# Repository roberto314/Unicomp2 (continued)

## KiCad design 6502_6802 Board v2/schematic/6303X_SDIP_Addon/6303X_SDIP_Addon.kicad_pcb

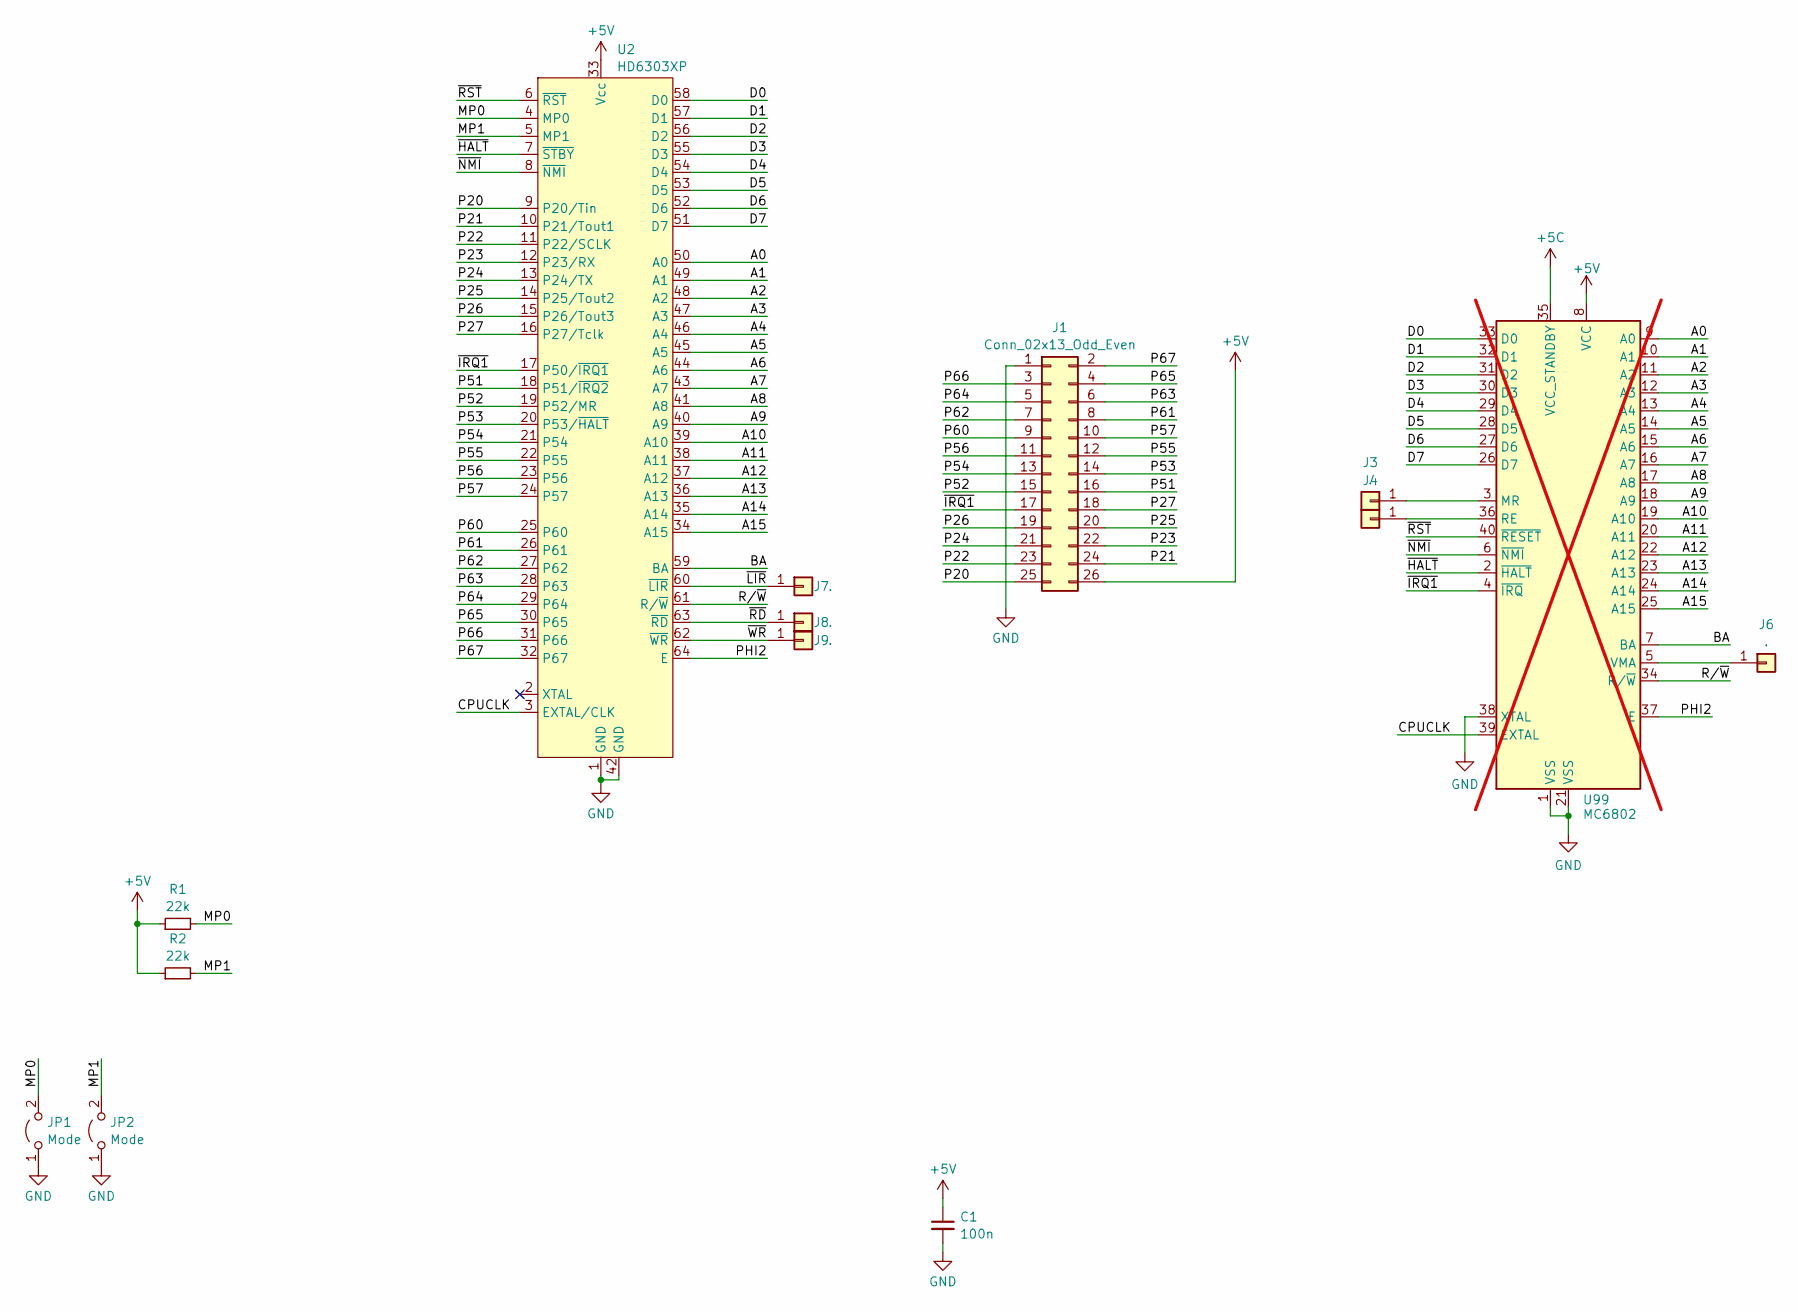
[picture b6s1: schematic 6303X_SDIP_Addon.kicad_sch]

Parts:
C1: 100n; C_1206_3216Metric_Pad1.33x1.80mm_HandSolder
J1: Conn_02x13_Odd_Even; PinHeader_2x13_P2.54mm_Horizontal
J3, J4, J6, J7, J8, J9: .; PinHeader_1x01_P2.00mm_Vertical
JP1, JP2: Mode; PinHeader_1x02_P2.54mm_Vertical
R1, R2: 22k; R_1206_3216Metric_Pad1.30x1.75mm_HandSolder
U2: HD6303XP; DIP-64_W19.05mm_P1.77
U99: MC6802; DIP-40_W15.24mm; not fitted

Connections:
+5V: C1.1, J1.26, R1.1, R2.1, U2.33 (Vcc); also elsewhere on the board
/A0: U2.50 (A0); also elsewhere on the board
/A1: U2.49 (A1); also elsewhere on the board
/A2: U2.48 (A2); also elsewhere on the board
/A3: U2.47 (A3); also elsewhere on the board
/A4: U2.46 (A4); also elsewhere on the board
/A5: U2.45 (A5); also elsewhere on the board
/A6: U2.44 (A6); also elsewhere on the board
/A7: U2.43 (A7); also elsewhere on the board
/A8: U2.41 (A8); also elsewhere on the board
/A9: U2.40 (A9); also elsewhere on the board
/A10: U2.39 (A10); also elsewhere on the board
/A11: U2.38 (A11); also elsewhere on the board
/A12: U2.37 (A12); also elsewhere on the board
/A13: U2.36 (A13); also elsewhere on the board
/A14: U2.35 (A14); also elsewhere on the board
/A15: U2.34 (A15); also elsewhere on the board
/BA: U2.59 (BA); also elsewhere on the board
/CPUCLK: U2.3 (EXTAL/CLK); also elsewhere on the board
/D0: U2.58 (D0); also elsewhere on the board
/D1: U2.57 (D1); also elsewhere on the board
/D2: U2.56 (D2); also elsewhere on the board
/D3: U2.55 (D3); also elsewhere on the board
/D4: U2.54 (D4); also elsewhere on the board
/D5: U2.53 (D5); also elsewhere on the board
/D6: U2.52 (D6); also elsewhere on the board
/D7: U2.51 (D7); also elsewhere on the board
/MP0: JP1.2 (B), R1.2, U2.4 (MP0)
/MP1: JP2.2 (B), R2.2, U2.5 (MP1)
/P20: J1.25, U2.9 (P20/Tin)
/P21: J1.24, U2.10 (P21/Tout1)
/P22: J1.23, U2.11 (P22/SCLK)
/P23: J1.22, U2.12 (P23/RX)
/P24: J1.21, U2.13 (P24/TX)
/P25: J1.20, U2.14 (P25/Tout2)
/P26: J1.19, U2.15 (P26/Tout3)
/P27: J1.18, U2.16 (P27/Tclk)
/P51: J1.16, U2.18 (P51/~IRQ2)
/P52: J1.15, U2.19 (P52/MR)
/P53: J1.14, U2.20 (P53/~HALT)
/P54: J1.13, U2.21 (P54)
/P55: J1.12, U2.22 (P55)
/P56: J1.11, U2.23 (P56)
/P57: J1.10, U2.24 (P57)
/P60: J1.9, U2.25 (P60)
/P61: J1.8, U2.26 (P61)
/P62: J1.7, U2.27 (P62)
/P63: J1.6, U2.28 (P63)
/P64: J1.5, U2.29 (P64)
/P65: J1.4, U2.30 (P65)
/P66: J1.3, U2.31 (P66)
/P67: J1.2, U2.32 (P67)
/PHI2: U2.64 (E); also elsewhere on the board
/R/~W: U2.61 (R/~W); also elsewhere on the board
/~HALT: U2.7 (~STBY); also elsewhere on the board
/~IRQ1: J1.17, U2.17 (P50/~IRQ1); also elsewhere on the board
/~LIR: J7.1, U2.60 (~LIR)
/~NMI: U2.8 (~NMI); also elsewhere on the board
/~RD: J8.1, U2.63 (~RD)
/~RST: U2.6 (~RST); also elsewhere on the board
/~WR: J9.1, U2.62 (~WR)
GND: C1.2, J1.1, JP1.1 (A), JP2.1 (A), U2.1 (GND), U2.42 (GND); also elsewhere on the board
unnamed 63: J3.1; also elsewhere on the board
unnamed 64: J4.1; also elsewhere on the board
unnamed 65: J6.1; also elsewhere on the board

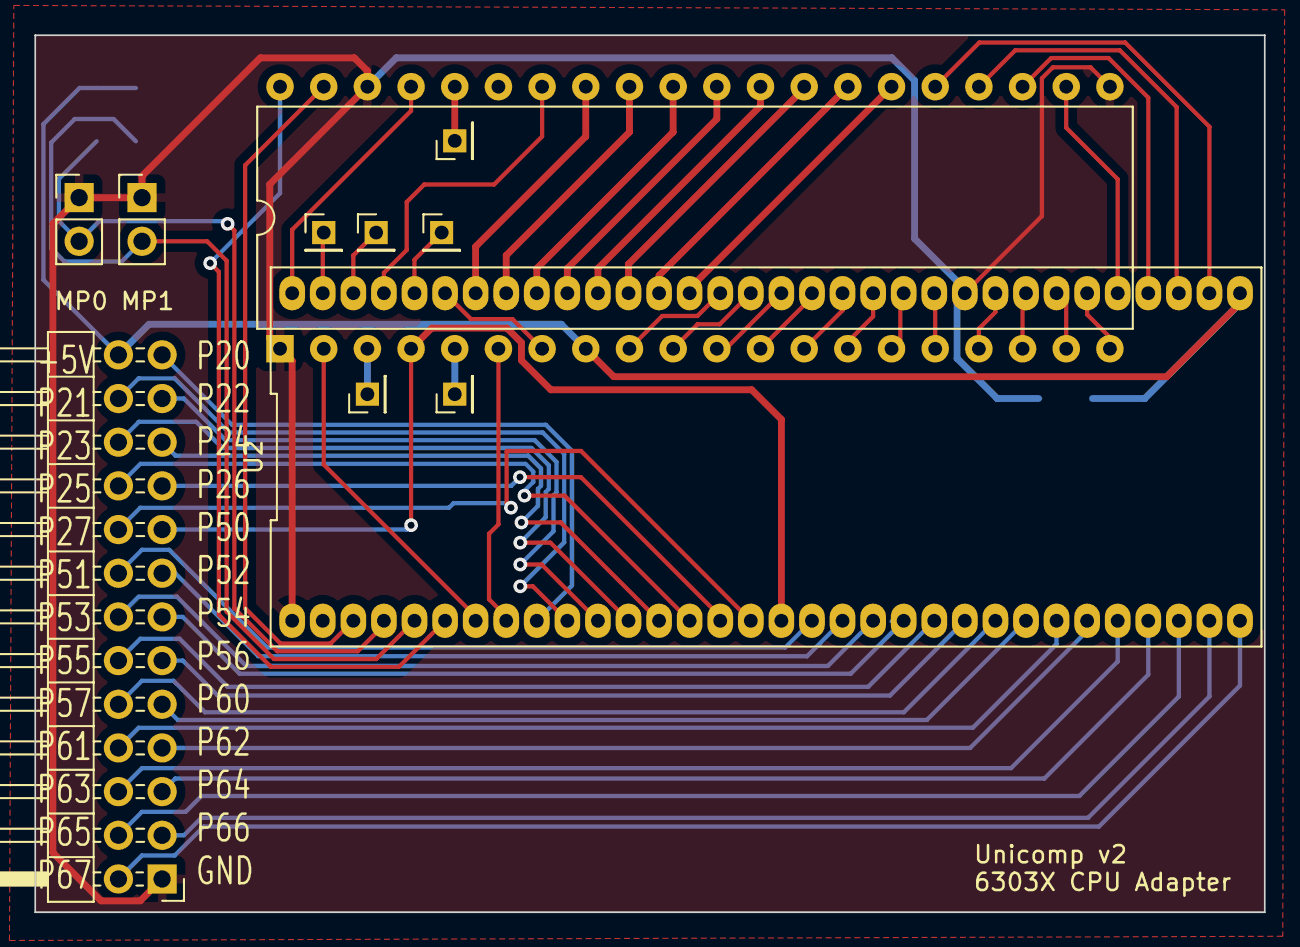
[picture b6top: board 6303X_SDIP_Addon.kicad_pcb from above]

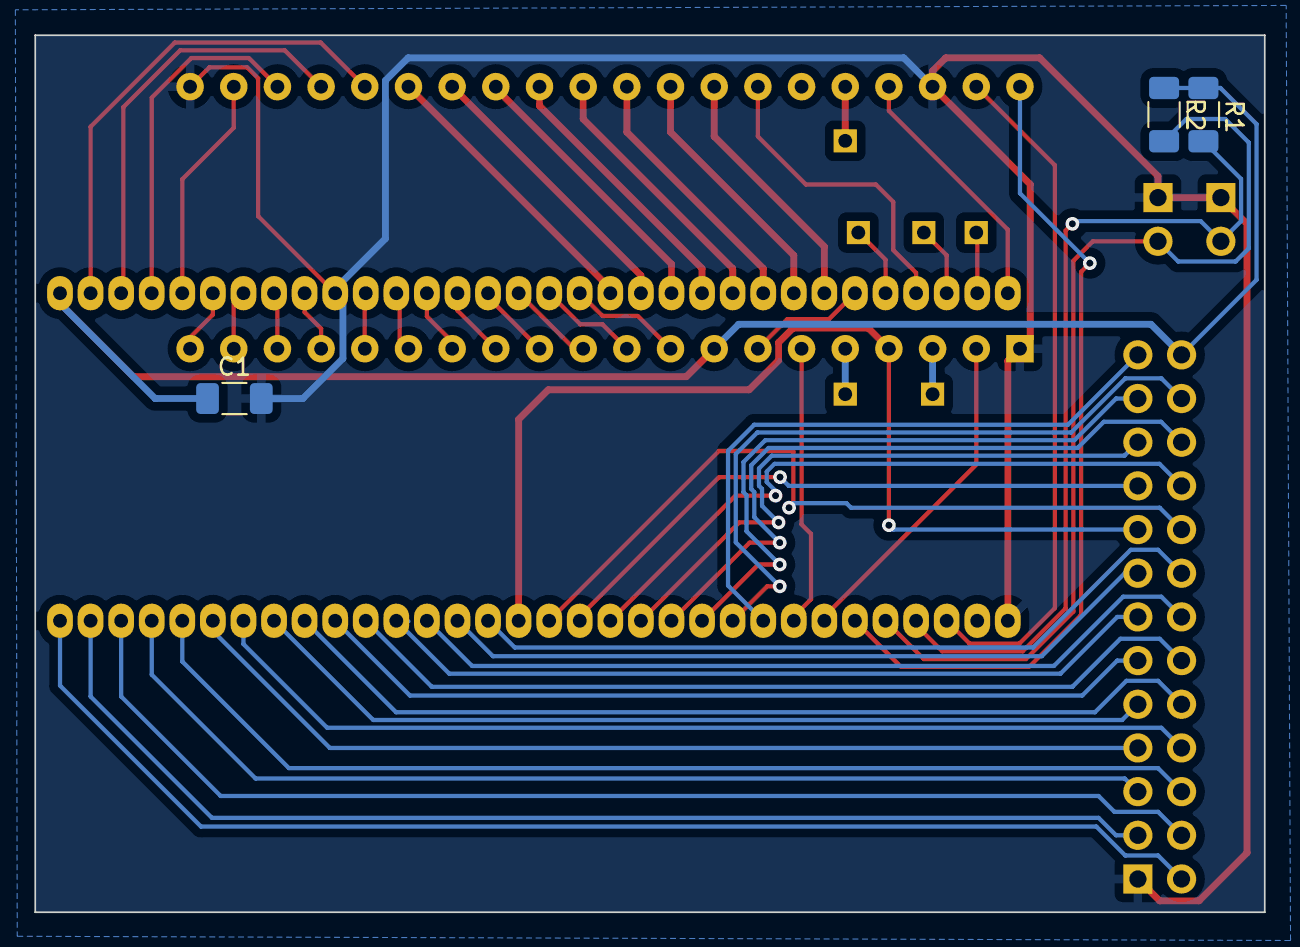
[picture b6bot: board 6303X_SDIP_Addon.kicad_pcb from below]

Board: 2 copper layers, 71.5 x 51.0 mm, 14 parts (3 on the bottom side), 65 nets.

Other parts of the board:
U3: MC6802; DIP-40_W15.24mm

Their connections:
+5V: U3.8 (VCC); also elsewhere on the board
/A0: U3.9 (A0); also elsewhere on the board
/A1: U3.10 (A1); also elsewhere on the board
/A2: U3.11 (A2); also elsewhere on the board
/A3: U3.12 (A3); also elsewhere on the board
/A4: U3.13 (A4); also elsewhere on the board
/A5: U3.14 (A5); also elsewhere on the board
/A6: U3.15 (A6); also elsewhere on the board
/A7: U3.16 (A7); also elsewhere on the board
/A8: U3.17 (A8); also elsewhere on the board
/A9: U3.18 (A9); also elsewhere on the board
/A10: U3.19 (A10); also elsewhere on the board
/A11: U3.20 (A11); also elsewhere on the board
/A12: U3.22 (A12); also elsewhere on the board
/A13: U3.23 (A13); also elsewhere on the board
/A14: U3.24 (A14); also elsewhere on the board
/A15: U3.25 (A15); also elsewhere on the board
/BA: U3.7 (BA); also elsewhere on the board
/CPUCLK: U3.39 (EXTAL); also elsewhere on the board
/D0: U3.33 (D0); also elsewhere on the board
/D1: U3.32 (D1); also elsewhere on the board
/D2: U3.31 (D2); also elsewhere on the board
/D3: U3.30 (D3); also elsewhere on the board
/D4: U3.29 (D4); also elsewhere on the board
/D5: U3.28 (D5); also elsewhere on the board
/D6: U3.27 (D6); also elsewhere on the board
/D7: U3.26 (D7); also elsewhere on the board
/PHI2: U3.37 (E); also elsewhere on the board
/R/~W: U3.34 (R/~W); also elsewhere on the board
/~HALT: U3.2 (~HALT); also elsewhere on the board
/~IRQ1: U3.4 (~IRQ); also elsewhere on the board
/~NMI: U3.6 (~NMI); also elsewhere on the board
/~RST: U3.40 (~RESET); also elsewhere on the board
GND: U3.1 (VSS), U3.21 (VSS), U3.38 (XTAL); also elsewhere on the board
unnamed 63: U3.3 (MR); also elsewhere on the board
unnamed 64: U3.36 (RE); also elsewhere on the board
unnamed 65: U3.5 (VMA); also elsewhere on the board

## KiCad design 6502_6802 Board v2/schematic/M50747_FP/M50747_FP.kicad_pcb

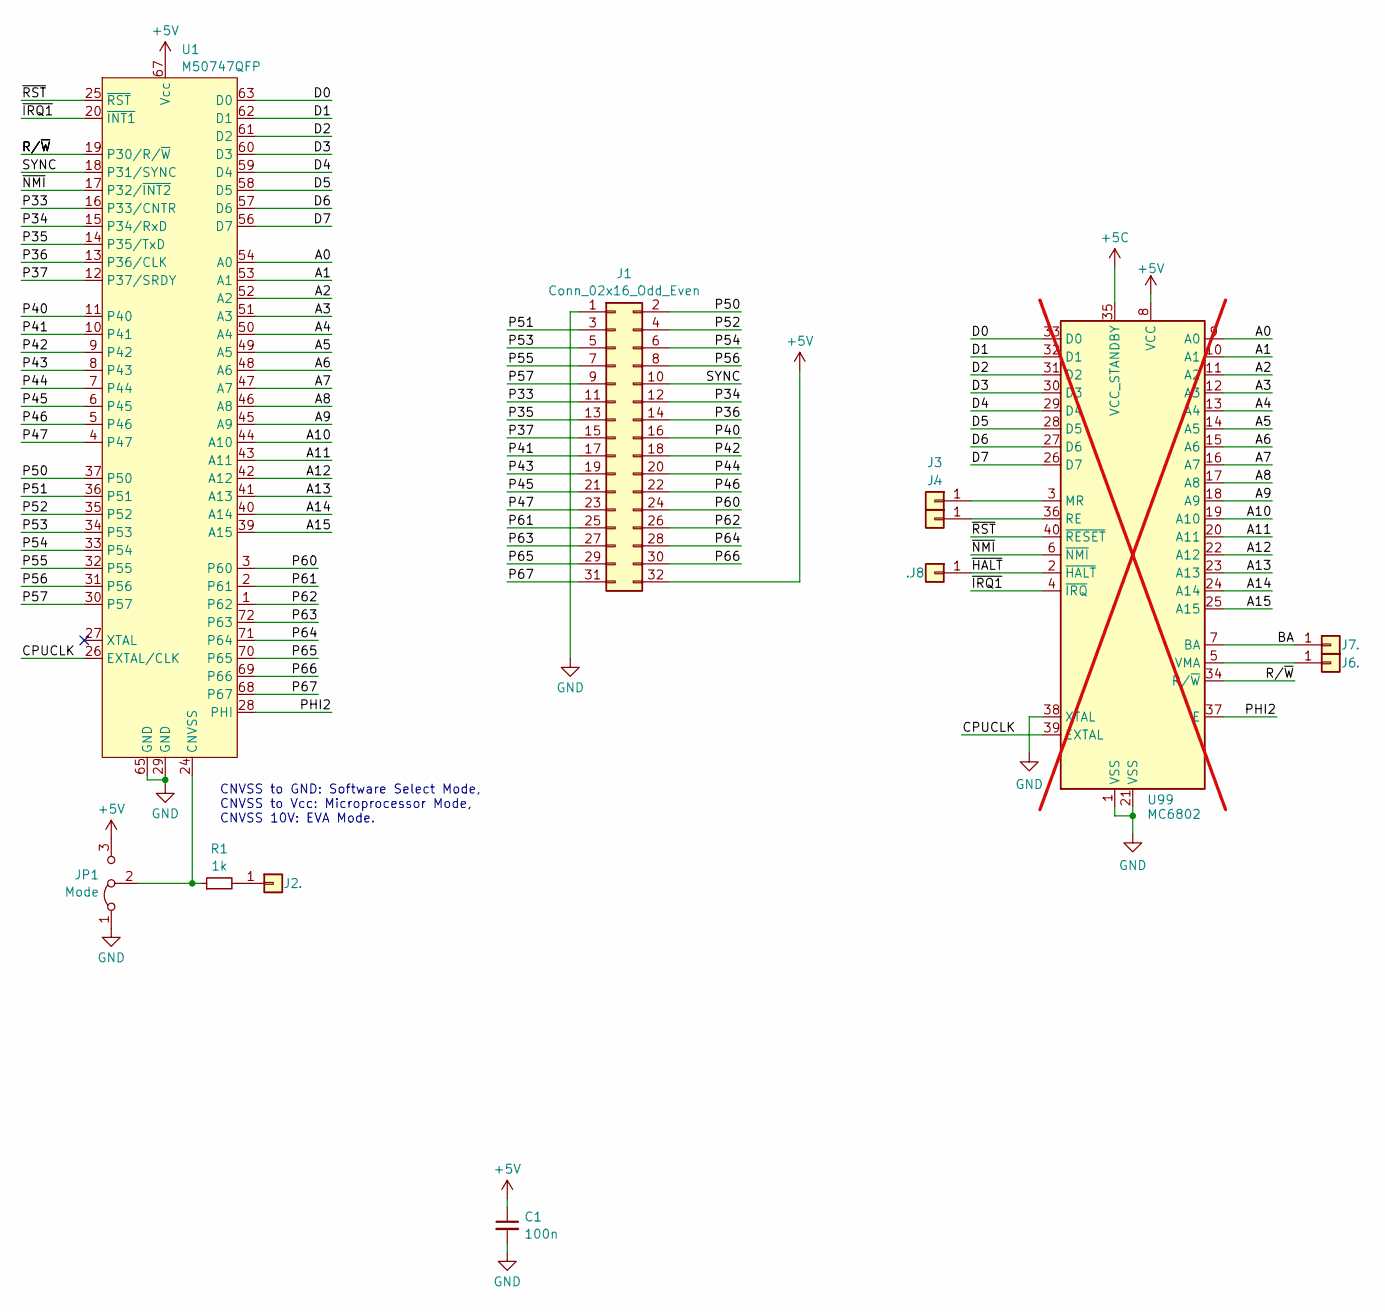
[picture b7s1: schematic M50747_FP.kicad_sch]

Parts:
C1: 100n; C_1206_3216Metric_Pad1.33x1.80mm_HandSolder
J1: Conn_02x16_Odd_Even; PinHeader_2x16_P2.54mm_Horizontal
J2, J3, J4, J6, J7, J8: .; PinHeader_1x01_P2.00mm_Vertical
JP1: Mode; SolderJumper-3_P1.3mm_Open_Pad1.0x1.5mm
R1: 1k; R_1206_3216Metric
U1: M50747QFP; QFP-72_13.2x18_Pitch0.8mm
U99: MC6802; DIP-40_W15.24mm; not fitted

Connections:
+5V: C1.1, J1.32, JP1.3 (B), U1.67 (Vcc); also elsewhere on the board
/A0: U1.54 (A0); also elsewhere on the board
/A1: U1.53 (A1); also elsewhere on the board
/A2: U1.52 (A2); also elsewhere on the board
/A3: U1.51 (A3); also elsewhere on the board
/A4: U1.50 (A4); also elsewhere on the board
/A5: U1.49 (A5); also elsewhere on the board
/A6: U1.48 (A6); also elsewhere on the board
/A7: U1.47 (A7); also elsewhere on the board
/A8: U1.46 (A8); also elsewhere on the board
/A9: U1.45 (A9); also elsewhere on the board
/A10: U1.44 (A10); also elsewhere on the board
/A11: U1.43 (A11); also elsewhere on the board
/A12: U1.42 (A12); also elsewhere on the board
/A13: U1.41 (A13); also elsewhere on the board
/A14: U1.40 (A14); also elsewhere on the board
/A15: U1.39 (A15); also elsewhere on the board
/BA: J7.1; also elsewhere on the board
/CPUCLK: U1.26 (EXTAL/CLK); also elsewhere on the board
/D0: U1.63 (D0); also elsewhere on the board
/D1: U1.62 (D1); also elsewhere on the board
/D2: U1.61 (D2); also elsewhere on the board
/D3: U1.60 (D3); also elsewhere on the board
/D4: U1.59 (D4); also elsewhere on the board
/D5: U1.58 (D5); also elsewhere on the board
/D6: U1.57 (D6); also elsewhere on the board
/D7: U1.56 (D7); also elsewhere on the board
/P33: J1.11, U1.16 (P33/CNTR)
/P34: J1.12, U1.15 (P34/RxD)
/P35: J1.13, U1.14 (P35/TxD)
/P36: J1.14, U1.13 (P36/CLK)
/P37: J1.15, U1.12 (P37/SRDY)
/P40: J1.16, U1.11 (P40)
/P41: J1.17, U1.10 (P41)
/P42: J1.18, U1.9 (P42)
/P43: J1.19, U1.8 (P43)
/P44: J1.20, U1.7 (P44)
/P45: J1.21, U1.6 (P45)
/P46: J1.22, U1.5 (P46)
/P47: J1.23, U1.4 (P47)
/P50: J1.2, U1.37 (P50)
/P51: J1.3, U1.36 (P51)
/P52: J1.4, U1.35 (P52)
/P53: J1.5, U1.34 (P53)
/P54: J1.6, U1.33 (P54)
/P55: J1.7, U1.32 (P55)
/P56: J1.8, U1.31 (P56)
/P57: J1.9, U1.30 (P57)
/P60: J1.24, U1.3 (P60)
/P61: J1.25, U1.2 (P61)
/P62: J1.26, U1.1 (P62)
/P63: J1.27, U1.72 (P63)
/P64: J1.28, U1.71 (P64)
/P65: J1.29, U1.70 (P65)
/P66: J1.30, U1.69 (P66)
/P67: J1.31, U1.68 (P67)
/PHI2: U1.28 (PHI); also elsewhere on the board
/R/~W: U1.19 (P30/R/~W); also elsewhere on the board
/SYNC: J1.10, U1.18 (P31/SYNC)
/~HALT: J8.1; also elsewhere on the board
/~IRQ1: U1.20 (~INT1); also elsewhere on the board
/~NMI: U1.17 (P32/~INT2); also elsewhere on the board
/~RST: U1.25 (~RST); also elsewhere on the board
GND: C1.2, J1.1, JP1.1 (A), U1.29 (GND), U1.65 (GND); also elsewhere on the board
unnamed: J2.1, R1.2
unnamed 66: J3.1; also elsewhere on the board
unnamed 67: J4.1; also elsewhere on the board
unnamed 68: J6.1; also elsewhere on the board
unnamed: JP1.2 (C), R1.1, U1.24 (CNVSS)

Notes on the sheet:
CNVSS to GND: Software Select Mode, CNVSS to Vcc: Microprocessor Mode, CNVSS 10V: EVA Mode.

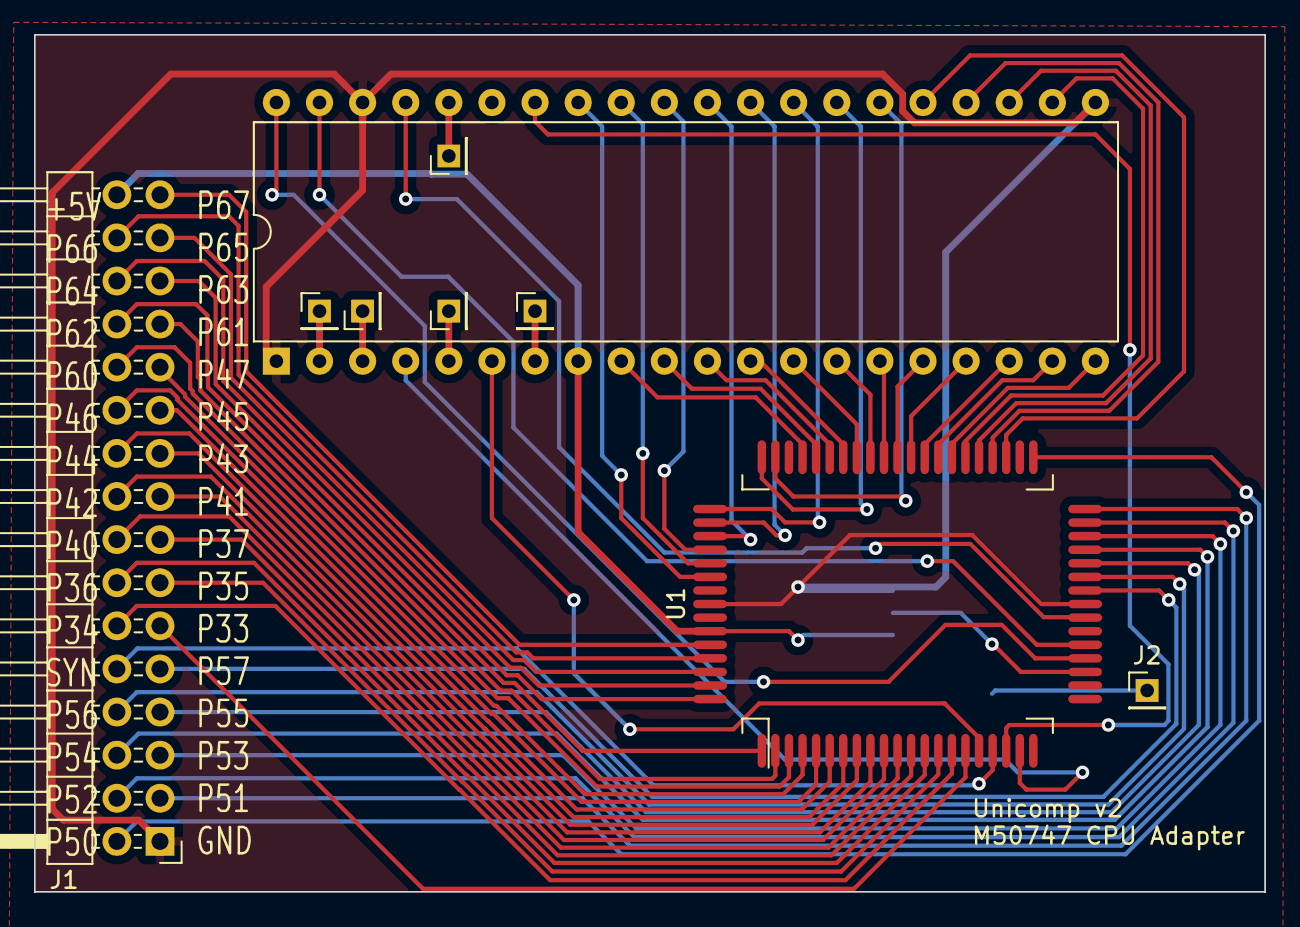
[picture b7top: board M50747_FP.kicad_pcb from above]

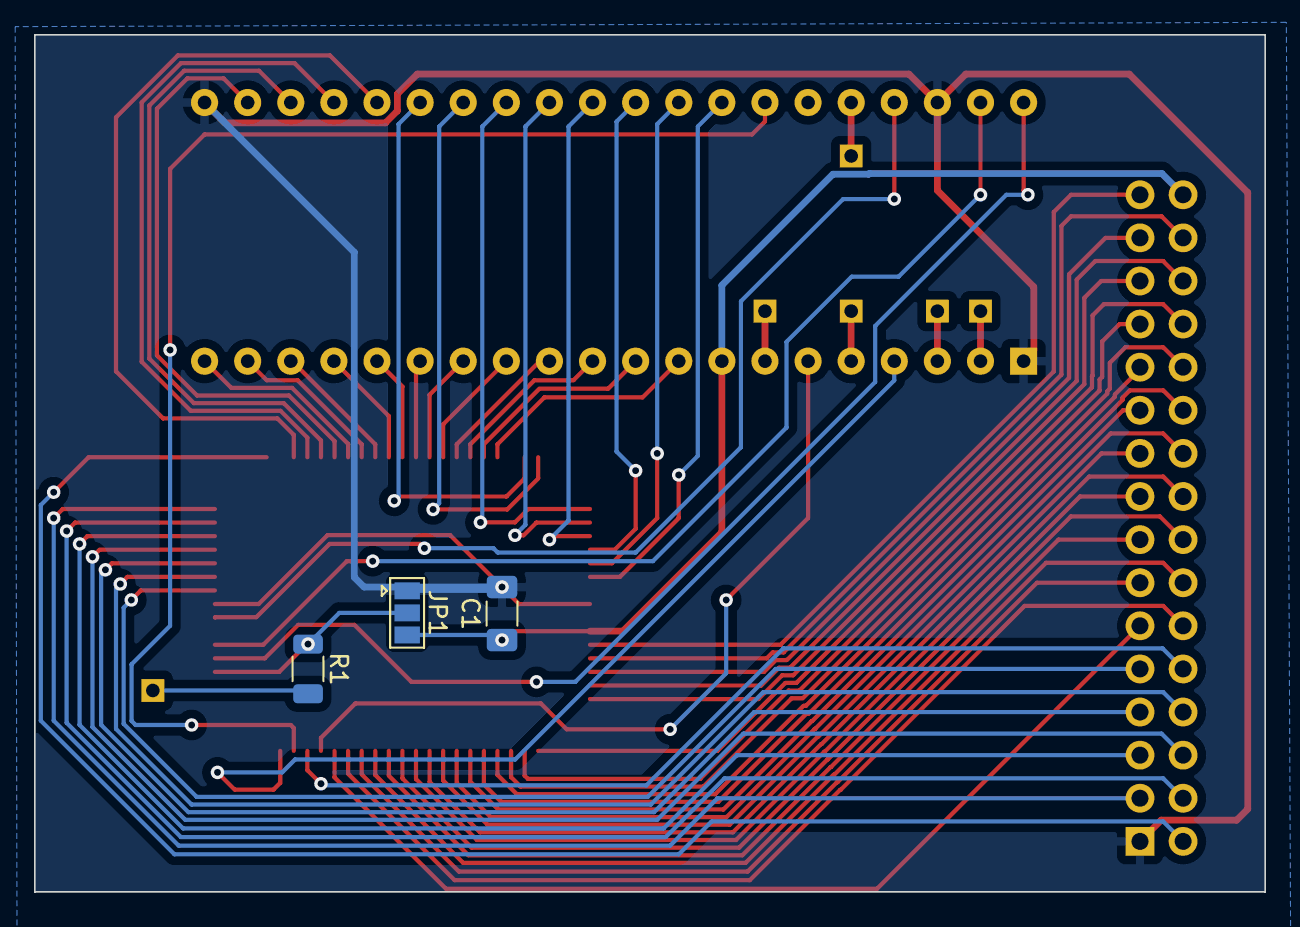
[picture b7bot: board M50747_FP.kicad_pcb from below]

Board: 2 copper layers, 72.5 x 50.5 mm, 12 parts (3 on the bottom side), 69 nets.

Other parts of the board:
U3: MC6802; DIP-40_W15.24mm

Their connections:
+5V: U3.8 (VCC); also elsewhere on the board
/A0: U3.9 (A0); also elsewhere on the board
/A1: U3.10 (A1); also elsewhere on the board
/A2: U3.11 (A2); also elsewhere on the board
/A3: U3.12 (A3); also elsewhere on the board
/A4: U3.13 (A4); also elsewhere on the board
/A5: U3.14 (A5); also elsewhere on the board
/A6: U3.15 (A6); also elsewhere on the board
/A7: U3.16 (A7); also elsewhere on the board
/A8: U3.17 (A8); also elsewhere on the board
/A9: U3.18 (A9); also elsewhere on the board
/A10: U3.19 (A10); also elsewhere on the board
/A11: U3.20 (A11); also elsewhere on the board
/A12: U3.22 (A12); also elsewhere on the board
/A13: U3.23 (A13); also elsewhere on the board
/A14: U3.24 (A14); also elsewhere on the board
/A15: U3.25 (A15); also elsewhere on the board
/BA: U3.7 (BA); also elsewhere on the board
/CPUCLK: U3.39 (EXTAL); also elsewhere on the board
/D0: U3.33 (D0); also elsewhere on the board
/D1: U3.32 (D1); also elsewhere on the board
/D2: U3.31 (D2); also elsewhere on the board
/D3: U3.30 (D3); also elsewhere on the board
/D4: U3.29 (D4); also elsewhere on the board
/D5: U3.28 (D5); also elsewhere on the board
/D6: U3.27 (D6); also elsewhere on the board
/D7: U3.26 (D7); also elsewhere on the board
/PHI2: U3.37 (E); also elsewhere on the board
/R/~W: U3.34 (R/~W); also elsewhere on the board
/~HALT: U3.2 (~HALT); also elsewhere on the board
/~IRQ1: U3.4 (~IRQ); also elsewhere on the board
/~NMI: U3.6 (~NMI); also elsewhere on the board
/~RST: U3.40 (~RESET); also elsewhere on the board
GND: U3.1 (VSS), U3.21 (VSS), U3.38 (XTAL); also elsewhere on the board
unnamed 66: U3.3 (MR); also elsewhere on the board
unnamed 67: U3.36 (RE); also elsewhere on the board
unnamed 68: U3.5 (VMA); also elsewhere on the board

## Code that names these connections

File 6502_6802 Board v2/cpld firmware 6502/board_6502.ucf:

NET "MOSI"  LOC = "p5"  ;
NET "SCK"   LOC = "p6"  ;
NET "A[0]"   LOC = "p30"  ;
NET "A[1]"   LOC = "p29"  ;
NET "A[2]"  LOC = "p28"  ;
NET "A[3]"  LOC = "p27"  ;
NET "A[4]"  LOC = "p23"  ;
NET "A[5]"  LOC = "p22"  ;
NET "A[6]"  LOC = "p21"  ;
NET "A[7]"  LOC = "p20"  ;
NET "A[8]"   LOC = "p19"  ;
NET "A[9]"   LOC = "p18"  ;
NET "A[10]"  LOC = "p16"  ;
NET "A[11]"  LOC = "p14"  ;
NET "A[12]"  LOC = "p13"  ;
NET "A[13]"  LOC = "p12"  ;
NET "A[14]"  LOC = "p8"  ;
NET "A[15]"  LOC = "p7"  ;

NET "RES0"  LOC = "p40"  ;
NET "RES1"  LOC = "p41"  ;
NET "RES2"  LOC = "p42"  ;

NET "nML"      LOC = "p39"  ;
NET "nBUSFREE" LOC = "p43"  ;
NET "nRST"     LOC = "p44"  ;
NET "PH0"      LOC = "p1"  ;
NET "nPH0"     LOC = "p2"  ;
NET "CLKF"     LOC = "p3"  ;
NET "nDOE"     LOC = "p31"  ;
NET "nAOE"     LOC = "p32"  ;
NET "nMWR"     LOC = "p33"  ;
NET "nMRD"     LOC = "p34"  ;
NET "RnW"      LOC = "p36"  ;
NET "PHI2CPU"  LOC = "p37"  ;
NET "PHI1CPU"  LOC = "p38"  ;

# ; NET "GND" LOC = "p4"  ;
# ; NET "TDI" LOC = "p9"  ;
# ; NET "TMS" LOC = "p10" ;
# ; NET "TCK" LOC = "p11" ;
# ; NET "VCC" LOC = "p15" ;
# ; NET "GND" LOC = "p17" ;
# ; NET "TDO" LOC = "p24" ;
# ; NET "GND" LOC = "p25" ;
# ; NET "VCC" LOC = "p26" ;
# ; NET "VCC" LOC = "p35" ;

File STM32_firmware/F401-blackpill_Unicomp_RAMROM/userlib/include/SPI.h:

/*
 * SPI.h
 *
 *  Created on: Nov 19, 2022
 *      Author: rob
 */

#ifndef USERLIB_INCLUDE_SPI_H_
#define USERLIB_INCLUDE_SPI_H_

#include "ch.h"
#include "hal.h"
#include "ostrich.h"

//typedef union {
//  uint32_t _32;
//  struct _8{
//    uint8_t _8l;
//    uint8_t _8lm;
//    uint8_t _8hm;
//    uint8_t _8h;
//  };
//}u_cv_t;

typedef struct {
    union {
      uint32_t _32;
      struct {
        uint8_t _8l;
        uint8_t _8lm;
        uint8_t _8hm;
        uint8_t _8h;
      };
    };
  uint8_t cs;
  uint8_t mask;
} st_configdata_t;

#define SPI_DRIVER   (&SPID1)
#define SPI_PORT     GPIOA
#define SCK_PAD      5  //PA5
#define MISO_PAD     6  //PA6
#define MOSI_PAD     7  //PA7
//#define CS_PORT      GPIOC
//#define CS_PAD       4

#define PLD           PAL_LINE(GPIOB, 12U) // Low: Load into Shift register
#define SEL0          PAL_LINE(GPIOC, 13U) // Select RAMWE
#define SEL1          PAL_LINE(GPIOC, 14U) // Select RAMWE
#define SEL2          PAL_LINE(GPIOC, 15U) // Select RAMWE
#define SEL4          PAL_LINE(GPIOA, 1U)  // Select RAMWE
#define ON_OFF        PAL_LINE(GPIOA, 0U)  // '138 Output On / Off = Write Enable
#define RAMOE         PAL_LINE(GPIOA, 4U)  // Ram Output Enable - Low Active
#define BUSFREE       PAL_LINE(GPIOB, 9U)  // Low if Bus is High-Z - Input
#define MRD           PAL_LINE(GPIOA, 15U) // Memory Read - Low Active
#define MWR           PAL_LINE(GPIOA, 9U)  // Memory Write - Low Active
#define CNT           PAL_LINE(GPIOA, 8U)  // Counter Tic
#define MRC           PAL_LINE(GPIOB, 15U) // Counter Reset - Low Active
#define CPR           PAL_LINE(GPIOB, 14U) // Counter Latch - Low Active
#define CNTOE         PAL_LINE(GPIOB, 13U) // Counter Output Enable - Low Active
#define TRESET        PAL_LINE(GPIOB, 10U) // Target Reset - High active
#define DEBUG         PAL_LINE(GPIOB, 0U)

#define PLD_IDLE palSetLine(PLD)
#define PLD_LOAD palClearLine(PLD)
#define WE_INACTIVE palSetLine(ON_OFF)
#define WE_ACTIVE palClearLine(ON_OFF)
#define CNT_ACTIVE palSetLine(CNT)
#define CNT_INACTIVE palClearLine(CNT)
#define MRC_INACTIVE palSetLine(MRC)
#define MRC_ACTIVE palClearLine(MRC)
#define CPR_INACTIVE palSetLine(CPR)
#define CPR_ACTIVE palClearLine(CPR)
#define CNTOE_INACTIVE palSetLine(CNTOE)
#define CNTOE_ACTIVE palClearLine(CNTOE)
#define RAMOE_ACTIVE palClearLine(RAMOE)
#define RAMOE_INACTIVE palSetLine(RAMOE)
#define TRESET_INACTIVE palClearLine(TRESET)
#define TRESET_ACTIVE palSetLine(TRESET)
#define DEBUG_HI palSetLine(DEBUG)
#define DEBUG_LOW palClearLine(DEBUG)

void SPI_init(void);
//void WriteSPI(int32_t val);
void write_single_byte(uint8_t data, int32_t address, uint8_t reset);
uint8_t read_single_byte(int32_t address, uint8_t reset);
uint8_t read_next_byte(void);
void write_next_byte(uint8_t data);
void read_block(int32_t address, int32_t len, uint8_t * data, uint8_t reset);
void write_block(int32_t address, int32_t len, uint8_t * data, uint8_t reset);
void write_config(uint8_t* buf);
void write_pins(uint8_t data);

#endif /* USERLIB_INCLUDE_SPI_H_ */

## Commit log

2023-07-25 Initial
2023-07-25 Readme update
2023-08-01 python work
2023-08-02 apple I test
2023-08-03 Apple I works, more Python work, uploadscripts for software done
2023-08-04 SYM1 & KIM1 work, RAM Board update
2023-08-04 MC6802 test
2023-08-05 c code change, MC6800 still not working
2023-08-06 Documentation update
2023-08-08 Documentation update, 6800 working, new computers added
2023-08-08 Documentation and pics update
2023-08-24 DREAM6800 video started
2023-08-27 DREAM6800 working with glitches
2023-08-31 SWTPC6800 working
2023-09-11 6809 Board done, Splitter Board new, RAMROM512k new
2023-09-17 i2c in stm32 implemented, python script canged
2023-10-04 olimex scripts updated
2023-10-04 python scripts updated
2024-01-12 MC3 Computer update
2024-02-13 some work on the CPU Adapter Boards
2024-05-14 Z80 added
2024-05-15 xsvf file creation added in 6502 board
